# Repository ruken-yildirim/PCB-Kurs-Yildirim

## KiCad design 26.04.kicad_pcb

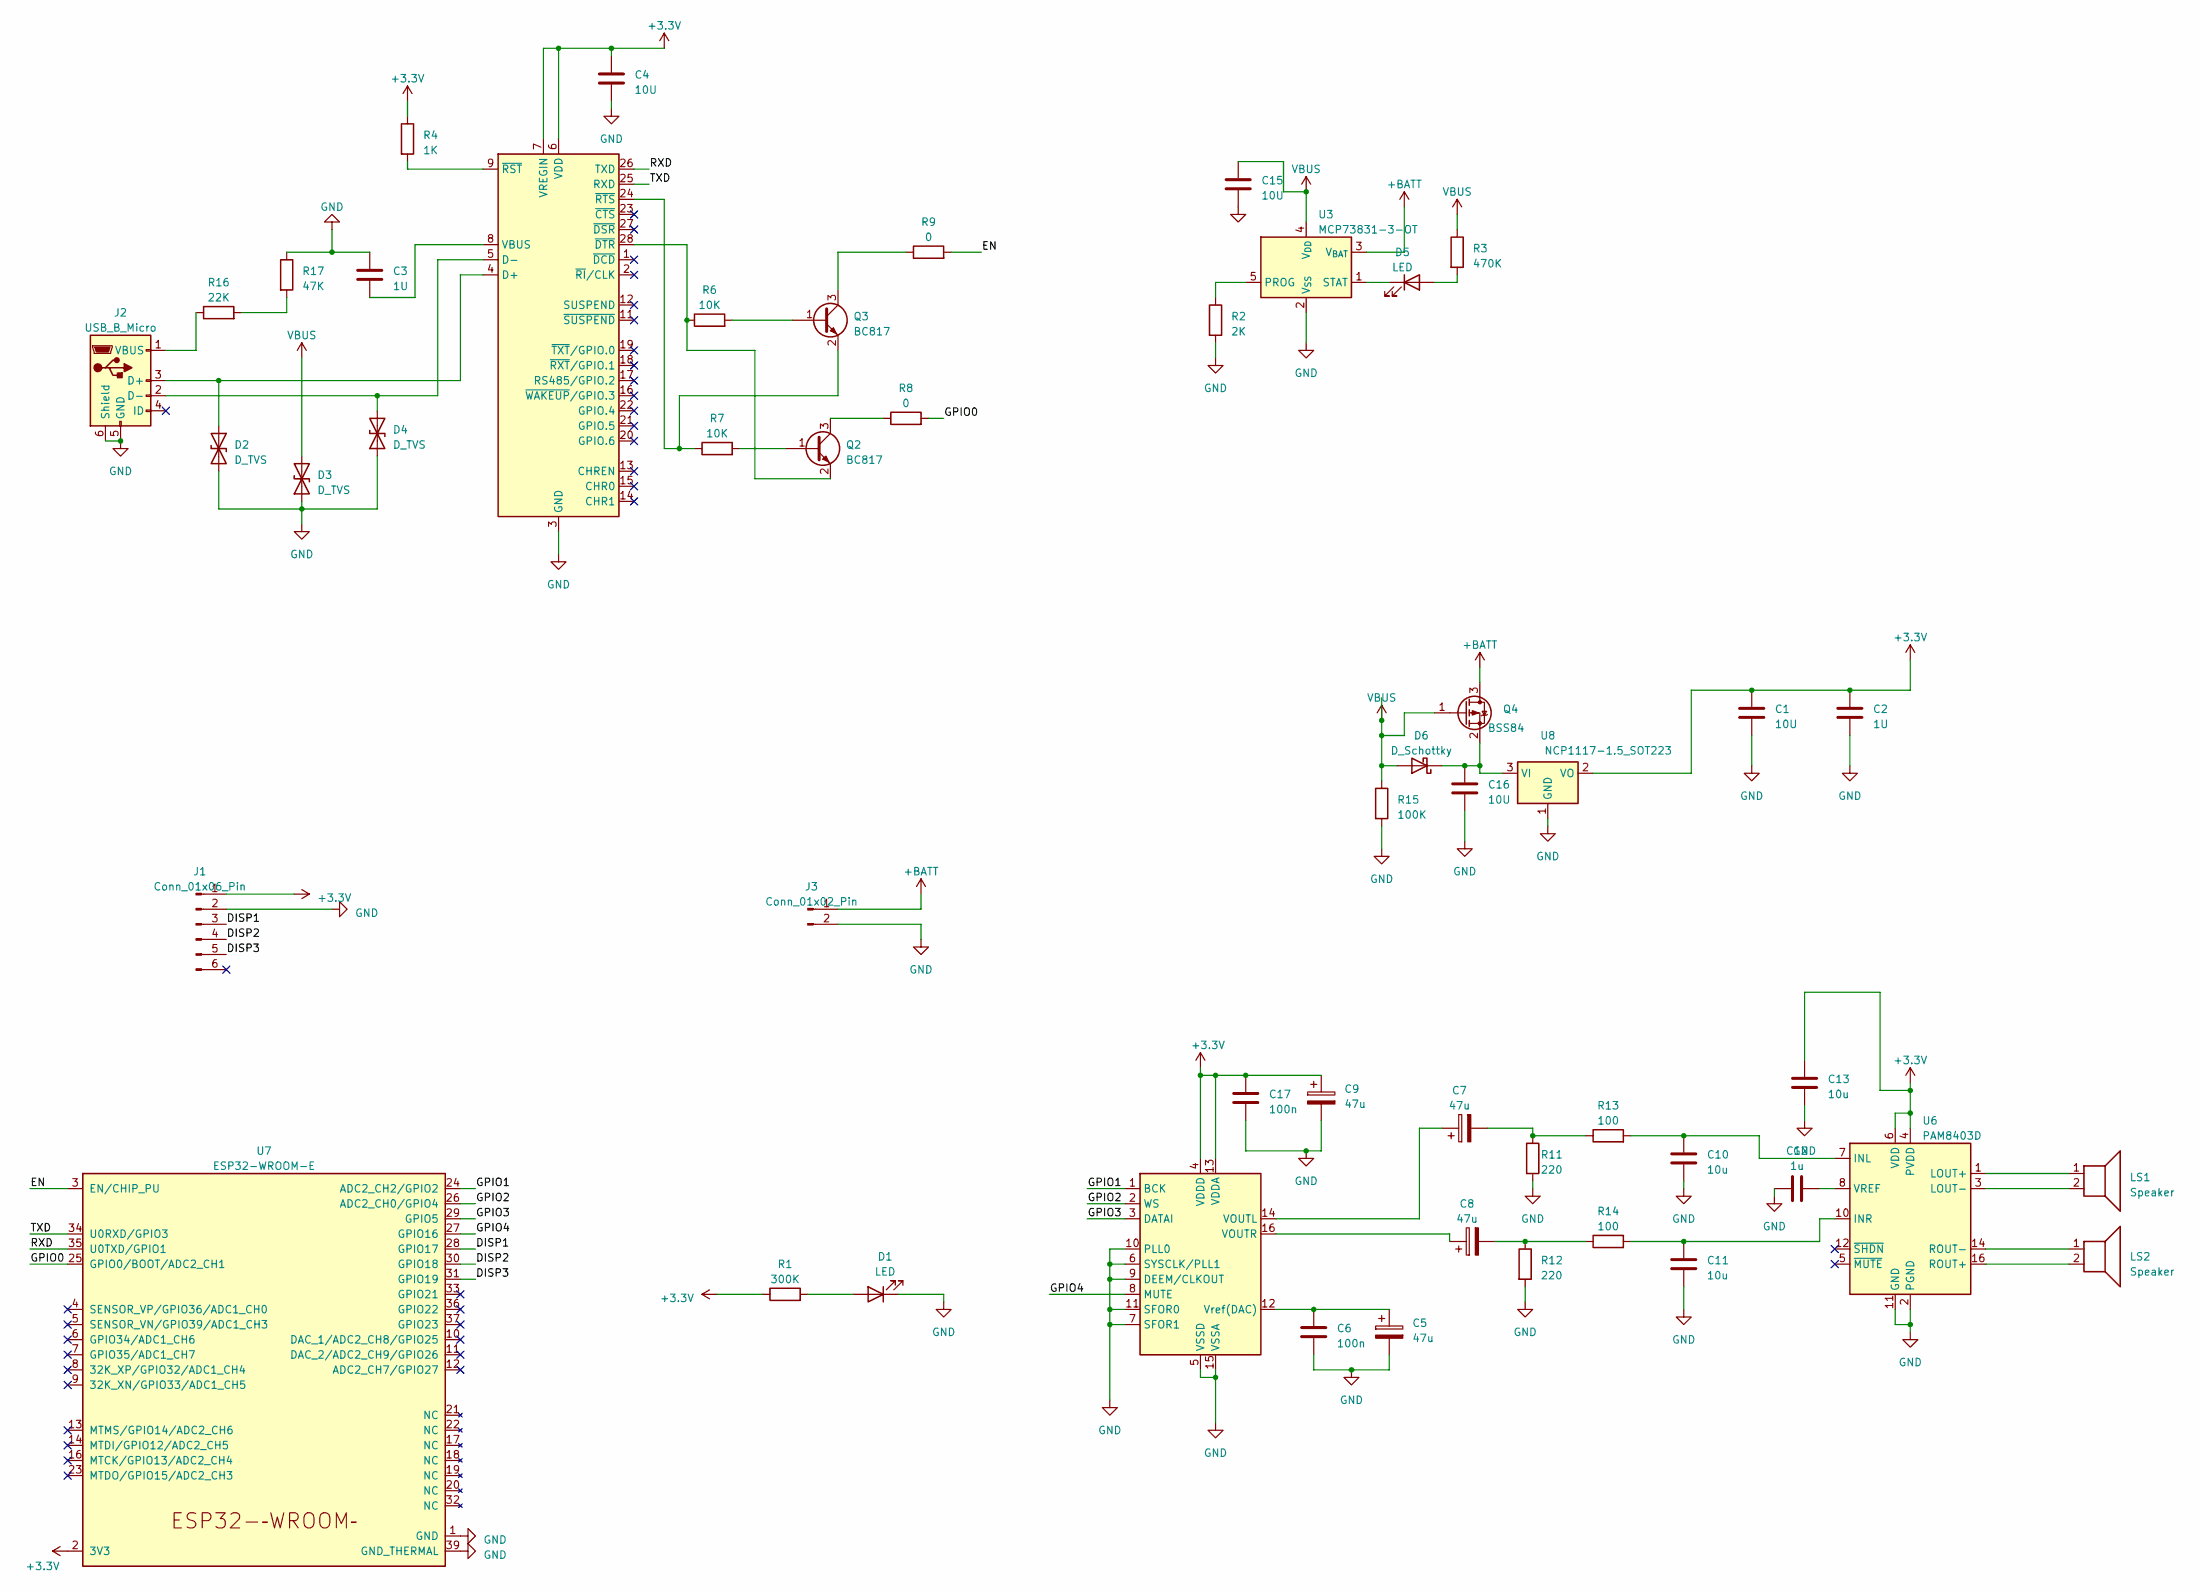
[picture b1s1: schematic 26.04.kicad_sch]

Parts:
C1, C4, C15, C16: 10U; C_0805_2012Metric
C2, C3: 1U; C_0805_2012Metric
C5, C7, C8, C9: 47u; C_Elec_8x10.2
C6, C17: 100n; C_0805_2012Metric
C10, C11, C13: 10u; C_0805_2012Metric
C12: 1u; C_0805_2012Metric
D1, D5: LED; LED_0805_2012Metric
D2, D3, D4: D_TVS; D_0603_1608Metric
D6: D_Schottky; D_SOD-123F
J1: Conn_01x06_Pin; PinHeader_1x06_P2.54mm_Vertical
J2: USB_B_Micro; USB_Micro-B_Molex-105017-0001
J3: Conn_01x02_Pin; PinHeader_1x02_P2.54mm_Vertical
LS1, LS2: Speaker; TerminalBlock_Altech_AK300-2_P5.00mm
Q2, Q3: BC817; SOT-23
Q4: BSS84; SOT-23
R1: 300K; R_0805_2012Metric
R2: 2K; R_0805_2012Metric
R3: 470K; R_0805_2012Metric
R4: 1K; R_0805_2012Metric
R6, R7: 10K; R_0805_2012Metric
R8, R9: 0; R_0805_2012Metric
R11, R12: 220; R_0805_2012Metric
R13, R14: 100; R_0805_2012Metric
R15: 100K; R_0805_2012Metric
R16: 22K; R_0805_2012Metric
R17: 47K; R_0805_2012Metric
U2: CP2102N-Axx-xQFN28; QFN-28-1EP_5x5mm_P0.5mm_EP3.35x3.35mm
U3: MCP73831-3-OT; SOT-23-5
U4: UDA1334ATS; SSOP-16_4.4x5.2mm_P0.65mm
U6: PAM8403D; SOP-16_3.9x9.9mm_P1.27mm
U7: ESP32-WROOM-E; ESP32-WROOM-32E
U8: NCP1117-1.5_SOT223; SOT-223-3_TabPin2

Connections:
+3.3V: C1.1, C2.1, C4.1, C9.1, C13.1, C17.1, J1.1, R1.1, R4.1, U2.6 (VDD), U2.7 (VREGIN), U4.4 (VDDD), U4.13 (VDDA), U6.4 (PVDD), U6.6 (VDD), U6.13 (PVDD), U7.2 (3V3), U8.2 (VO)
+BATT: J3.1, Q4.3 (D), U3.3 (V_{BAT})
/DISP1: J1.3, U7.28 (GPIO17)
/DISP2: J1.4, U7.30 (GPIO18)
/DISP3: J1.5, U7.31 (GPIO19)
/EN: R9.2, U7.3 (EN/CHIP_PU)
/GPIO0: R8.2, U7.25 (GPIO0/BOOT/ADC2_CH1)
/GPIO1: U4.1 (BCK), U7.24 (ADC2_CH2/GPIO2)
/GPIO2: U4.2 (WS), U7.26 (ADC2_CH0/GPIO4)
/GPIO3: U4.3 (DATAI), U7.29 (GPIO5)
/GPIO4: U4.8 (MUTE), U7.27 (GPIO16)
/RXD: U2.26 (TXD), U7.35 (U0TXD/GPIO1)
/TXD: U2.25 (RXD), U7.34 (U0RXD/GPIO3)
GND: C1.2, C2.2, C3.1, C4.2, C5.2, C6.2, C9.2, C10.2, C11.2, C12.1, C13.2, C15.2, C16.2, C17.2, D1.1 (K), D2.2 (A2), D3.1 (A1), D4.1 (A1), J1.2, J2.5 (GND), J2.6 (Shield), J3.2, R2.2, R11.2, R12.2, R15.2, R17.1, U2.3 (GND), U2.29 (GND), U3.2 (V_{SS}), U4.5 (VSSD), U4.6 (SYSCLK/PLL1), U4.7 (SFOR1), U4.9 (DEEM/CLKOUT), U4.10 (PLL0), U4.11 (SFOR0), U4.15 (VSSA), U6.2 (PGND), U6.11 (GND), U6.15 (PGND), U7.1 (GND), U7.15 (GND), U7.38 (GND), U7.39 (GND_THERMAL), U8.1 (GND)
unnamed: C7.2, R11.1, R13.1
unnamed: C8.2, R12.1, R14.1
unnamed: D1.2 (A), R1.2
unnamed: D2.1 (A1), J2.3 (D+), U2.4 (D+)
unnamed: D4.2 (A2), J2.2 (D-), U2.5 (D-)
unnamed: D5.2 (A), R3.2
unnamed: D5.1 (K), U3.1 (STAT)
unnamed: C16.1, D6.1 (K), Q4.2 (S), U8.3 (VI)
unnamed: J2.1 (VBUS), R16.1
unnamed: Q2.1 (B), R7.2
unnamed: Q2.3 (C), R8.1
unnamed: Q2.2 (E), R6.1, U2.28 (~DTR)
unnamed: Q3.1 (B), R6.2
unnamed: Q3.3 (C), R9.1
unnamed: Q3.2 (E), R7.1, U2.24 (~RTS)
unnamed: R16.2, R17.2
unnamed: C3.2, U2.8 (VBUS)
unnamed: R4.2, U2.9 (~RST)
unnamed: R2.1, U3.5 (PROG)
unnamed: C7.1, U4.14 (VOUTL)
unnamed: C8.1, U4.16 (VOUTR)
unnamed: C5.1, C6.1, U4.12 (Vref(DAC))
unnamed: C10.1, R13.2, U6.7 (INL)
unnamed: C11.1, R14.2, U6.10 (INR)
unnamed: LS1.1, U6.1 (LOUT+)
unnamed: LS1.2, U6.3 (LOUT-)
unnamed: LS2.2, U6.16 (ROUT+)
unnamed: LS2.1, U6.14 (ROUT-)
unnamed: C12.2, U6.8 (VREF)
VBUS: C15.1, D3.2 (A2), D6.2 (A), Q4.1 (G), R3.1, R15.1, U3.4 (V_{DD})

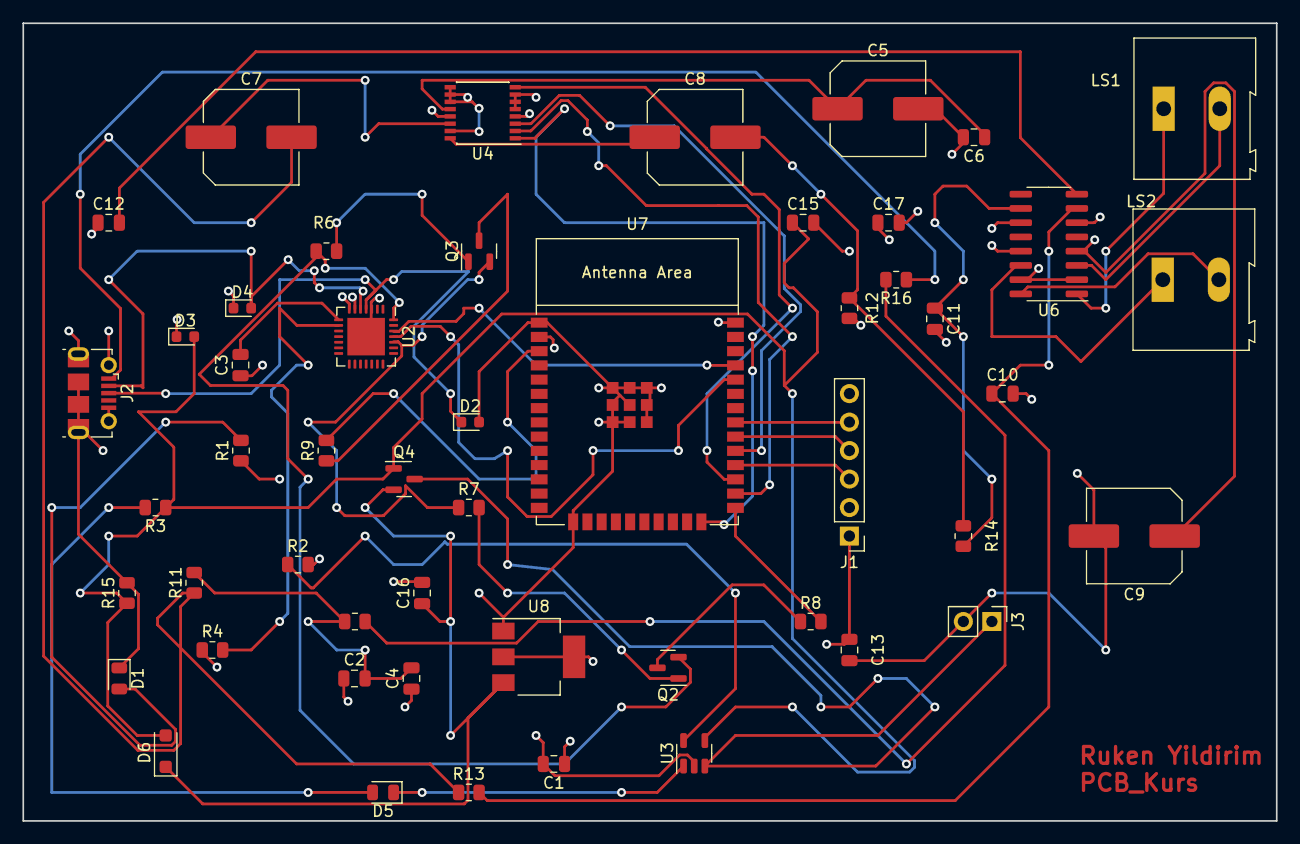
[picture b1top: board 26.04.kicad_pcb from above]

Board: 4 copper layers, 111.8 x 71.1 mm, 51 parts (0 on the bottom side), 44 nets.
